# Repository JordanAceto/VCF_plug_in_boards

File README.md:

# Various Voltage Controlled Filter pcbs

- #### These small VCF "plug-in" boards each contain a filter "core". These are intended to be plugged into a motherboard which provides a +/- 12 volt power supply, input/output circuitry, and control voltage sources.
- #### They all share an identical mechanical and electrical format.
- #### The intended use is to make a bunch of different filters and then be able to easily try them out by swapping the filter plug-in boards into the motherboard.

## The mechanical format and pinout shared by all plug-in boards:

## Signal levels:
- #### The plug-in boards are expecting modular synthesizer level signals of around +/- 5 volts.
- #### Many filters have interesting resonance and distortion characteristics that depend on signal level. Experiment with increasing and decreasing the signal levels to find the sweet spots.
- #### The output signal may or may not be in phase with the input signal.

## CV signals:
- #### The motherboard is expected to provide a 0 to +2.048 volt cutoff frequency CV signal. The plug-in boards are designed to sweep through their entire range with this range, with 0 volts mapping to the lowest cutoff frequency (usually around 20Hz) and +2.048 volts mapping to the highest cutoff frequency (usually around 20kHz).
- #### The feedback CV from the motherboard uses the same range: 0 volts of feedback CV maps to "no feedback" and +2.048 volts of feedback CV maps to maximum feedback.
- #### The CV range of 0 to +2.048 volts was chosen becuase it allows the cutoff and feedback CV signals to be conveniently driven directly from a cheap MCP4822 DAC. Don't worry about an exact 2.048 volt range, the filters have trimmers to account for variations.
- #### If different scalings are desired it is usually fairly trivial to change some resistor values in the CV scaling circuits on the plug-in boards.

## Feedback considerations:
- #### The plug-in boards all have voltage controlled feedback. This makes it easier to swap them in and out of a motherboard without worrying about the type and value of feedback potentiometer.
- #### This also makes it easier to apply "Q-compensation" to 4-pole low pass filters that suffer from passband attenuation when feedback is increased.
- #### All 4-pole filters have some form of Q-compensation built in. The builder can usually adjust the amount of compensation, or choose no compensation at all by changing a single resistor.

## Calibration:
- #### Each plug-in board has calibration trimpots for modulation depth, center frequency, and feedback sensitivity.
- #### For filters that can track at 1 volt per octave, they can probably be trimmed to play in tune over a limited range, but the trimming may be fiddly. Emphasis has been placed on getting a nice sweep through the filters useful range, and not accurate tuning or temperature compensation.
- #### Calibration is a matter of taste, and any setup that sounds good to you is correct.
- #### Here is how I calibrate Low Pass Filters:
    1. Inject a 30Hz square wave onto the signal input while monitoring the signal output.
    2. Turn the cutoff CV and feedback CV signals all the way down (set them to zero volts).
    3. Adjust the **center** trim so that the signal just dissapears.
    4. Remove the signal input.
    5. Turn the cutoff CV to around 1/2 way up and turn the feedback CV all the way up.
    6. Adjust the **feedback** trim until self oscillation occurs.
    7. Turn the cutoff CV signal all the way up.
    8. Adjust the **depth** trim until the frequency of the self oscillation is around 20kHz.
    9. Sweep the cutoff frequency up and down and readjust the **feedback** trim as needed to get reliable self oscillation over the desired range. Note that some filters will not self oscillate over their whole frequency range.
    10. Now reinject the signal and listen to the filter while changing the cutoff and feedack CV signals. Readjust the trimmers to taste if desired.

- #### I use a similar strategy for other filter topologies like Phase Shifters. Without a self oscillation signal or a strong sense of "cutoff frequency", just adjust the trimmers so that the filter has a nice sweep and the feedback control feels good.
- #### The above calibration strategy is very quick and easy once you've done it a few times.

## Power supply considerations:
- #### The motherboard is expected to provide a +/-12 volt DC power supply.
- #### Current draw varies across the filter boards from a handfull of milliamps to a few 10's of milliamps.
- #### Ensure that the motherboard can supply at least 100mA or so on each rail.

## Starting new plug-in board pcbs:
- #### A template is provided to make it easy to start new plug-in board filters.
- #### This template contains a standard directory structure, and the start of a kicad project.
- #### The template kicad docs have the skeleton of the schematic and pcb.

## Project structure:
- #### Each filter plug-in board subdirectory follows a consistent structure:
    - #### `kicad_docs/` contains the files needed to open and edit the filter schematic and pcb layout using kicad.
    - #### `construction_docs/` contains a pdf copy of the schematic, an interactive BOM which can be opened in a web browser, and gerbers.
    - #### `pics/` contains a few rendered pics of the pcb.
- #### Basically, if you want to edit the filter go into `kicad_docs/`, if you want to build the filter go into `construction_docs/`.
- #### Note that the filters may be a work in progress and may not contain complete documentation until they are done.
- #### See the board status checklist below, any board that is not checked all the way across is likely to contain errors. Boards that are all checked all the way across are safe to build.

## Status of the boards:

Board | breadboarded | schematic | pcb layout | built and tested | documentation
------|--------------|-----------|------------|------------------|---------------
[2164 phasor](https://github.com/JordanAceto/VCF_plug_in_boards/tree/master/2164_phasor_plug_in_board)       | &#9745; | &#9745; | &#9745; | &#9745; | &#9745;
[2164 LPF](https://github.com/JordanAceto/VCF_plug_in_boards/tree/master/2164_4_pole_LPF_plug_in_board)       | &#9745; | &#9745; | &#9745; | &#9745; | &#9745;
[2164 SVF](https://github.com/JordanAceto/VCF_plug_in_boards/tree/master/2164_SVF_plug_in_board)       | &#9745; | &#9745; | &#9745; | &#9745; | &#9745;
[arp 4072 LPF](https://github.com/JordanAceto/VCF_plug_in_boards/tree/master/arp_4072_LPF_plug_in_board)      | &#9745; | &#9745; | &#9745; | &#9745; | &#9745;
[CEM3320 LPF](https://github.com/JordanAceto/VCF_plug_in_boards/tree/master/CEM3320_LPF_plug_in_board)       | &#9745; | &#9745; | &#9745; | &#9745; | &#9745;
[haible 2040 LPF](https://github.com/JordanAceto/VCF_plug_in_boards/tree/master/haible_2040_LPF_plug_in_board)   | &#9745; | &#9744; | &#9744; | &#9744; | &#9744;
[haible tau phasor](https://github.com/JordanAceto/VCF_plug_in_boards/tree/master/haible_tau_phaser_plug_in_board/kicad_docs) | &#9744; | &#9744; | &#9744; | &#9744; | &#9744;
[Late MS20 VCF](https://github.com/JordanAceto/VCF_plug_in_boards/tree/master/late_MS20_VCF_plug_in_board)       | &#9745; | &#9745; | &#9745; | &#9745; | &#9745;
[minimoog LPF](https://github.com/JordanAceto/VCF_plug_in_boards/tree/master/minimoog_LPF_plug_in_board)      | &#9745; | &#9745; | &#9745; | &#9745; | &#9745;
[mutron 3 SVF](https://github.com/JordanAceto/VCF_plug_in_boards/tree/master/mutron_III_plug_in_board)      | &#9745; | &#9745; | &#9745; | &#9745; | &#9745;
[optical phasor](https://github.com/JordanAceto/VCF_plug_in_boards/tree/master/optical_phasor_plug_in_board)    | &#9745; | &#9745; | &#9745; | &#9745; | &#9745;
[SSI2140 LPF](https://github.com/JordanAceto/VCF_plug_in_boards/tree/master/SSI2140_LPF_plug_in_board) | &#9745; | &#9745; | &#9745; | &#9745; | &#9745;

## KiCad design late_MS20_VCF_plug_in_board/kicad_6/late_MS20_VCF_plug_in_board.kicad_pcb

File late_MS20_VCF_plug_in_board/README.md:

# Late MS20 style VCF Plug-In Board

Small MS20 based low pass/high pass filter PCB, designed to plug into a larger motherboard.

## Details

MS20 based LPF/HPF with voltage controlled feedback. This PCB includes the audio path and CV inputs for frequency and feedback, but does not include any modulation sources.

The intended use for this board is to plug in to a larger motherboard which contains slots for one or more of these plug-in boards, as well as modulation sources, panel controls, and input/output routing.

High pass or Low pass mode is selected by placing two jumpers as indicated on the silkscreen.

## Inputs

-Audio in: dry audio input to be filtered.

-Frequency CV in: 0 volts to +2.048 volts, higher voltage = higher sweep.

-Feedback CV in: 0 volts to +2.048 volts, higher voltage = more feedback.

## Outputs

-Audio out: filtered audio output.

## Filter mode selection

- This filter has two filter modes available: Low Pass and High Pass.

- One mode at a time can be selected by placing two jumpers according to the silkscreen.

## Power Supply Requirements

A bipolar 12 volt power supply is required. This will typically come from the motherboard.

## Calibration

- See the top level README for calibration instructions.

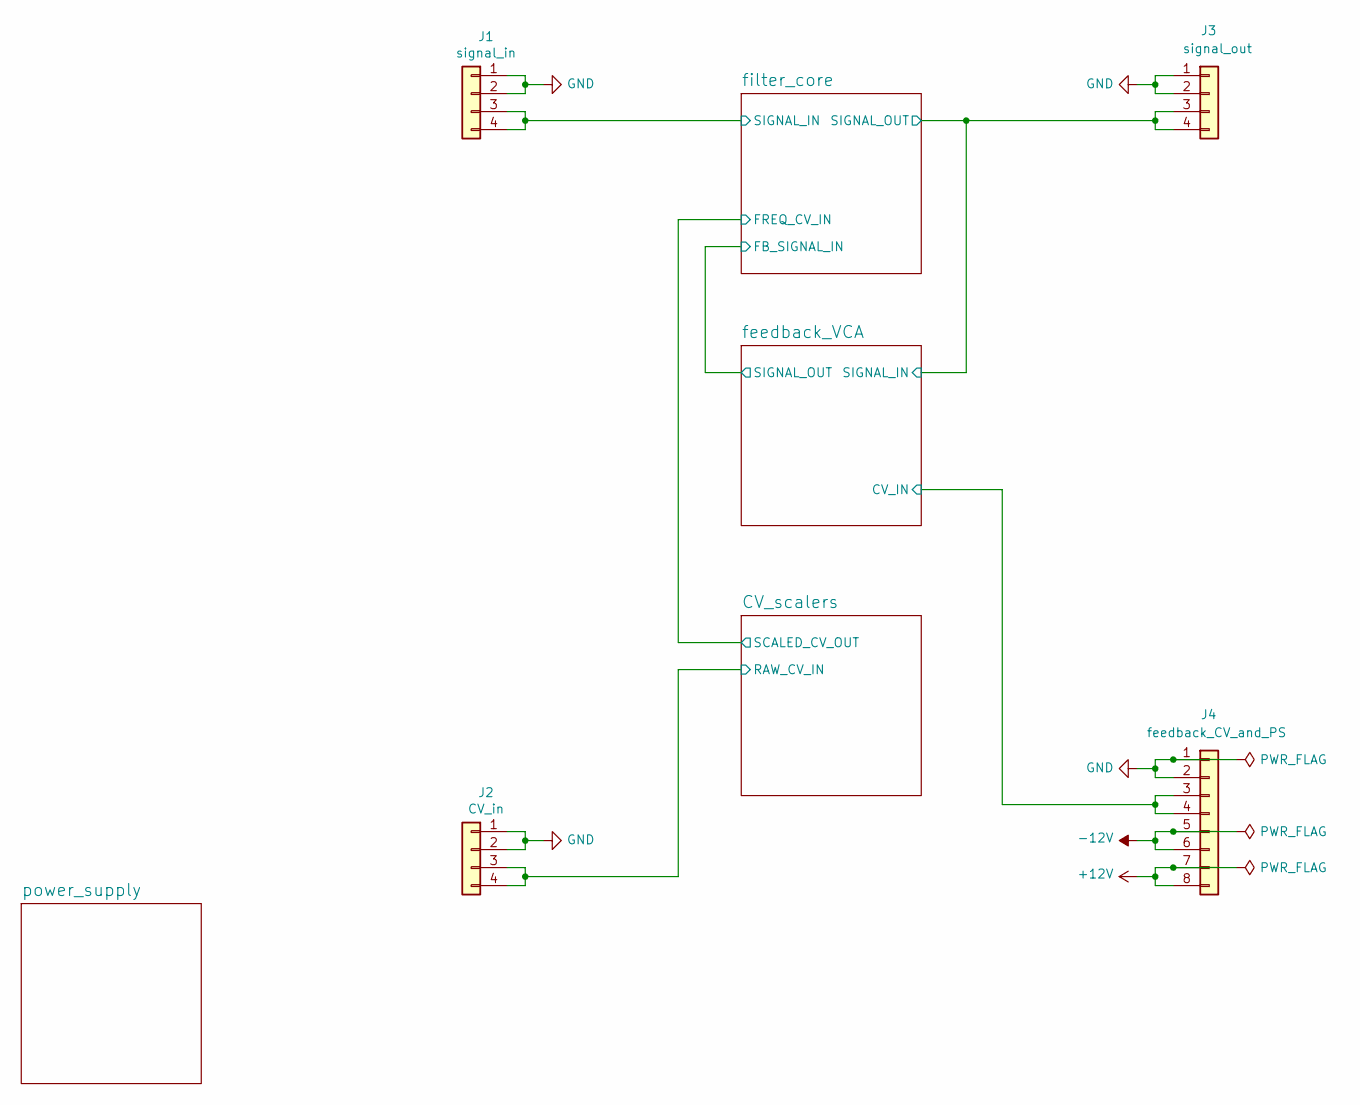
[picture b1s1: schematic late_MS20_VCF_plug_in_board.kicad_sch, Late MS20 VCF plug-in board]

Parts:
J1: signal_in; PinHeader_1x04_P2.54mm_Vertical
J2: CV_in; PinHeader_1x04_P2.54mm_Vertical
J3: signal_out; PinHeader_1x04_P2.54mm_Vertical
J4: feedback_CV_and_PS; PinHeader_1x08_P2.54mm_Vertical

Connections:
+12V: J4.7, J4.8; also elsewhere on the board
-12V: J4.5, J4.6; also elsewhere on the board
/CV_scalers/RAW_CV_IN: J2.3, J2.4; also elsewhere on the board
/feedback_VCA/CV_IN: J4.3, J4.4; also elsewhere on the board
/feedback_VCA/SIGNAL_IN: J3.3, J3.4; also elsewhere on the board
/filter_core/SIGNAL_IN: J1.3, J1.4; also elsewhere on the board
GND: J1.1, J1.2, J2.1, J2.2, J3.1, J3.2, J4.1, J4.2; also elsewhere on the board

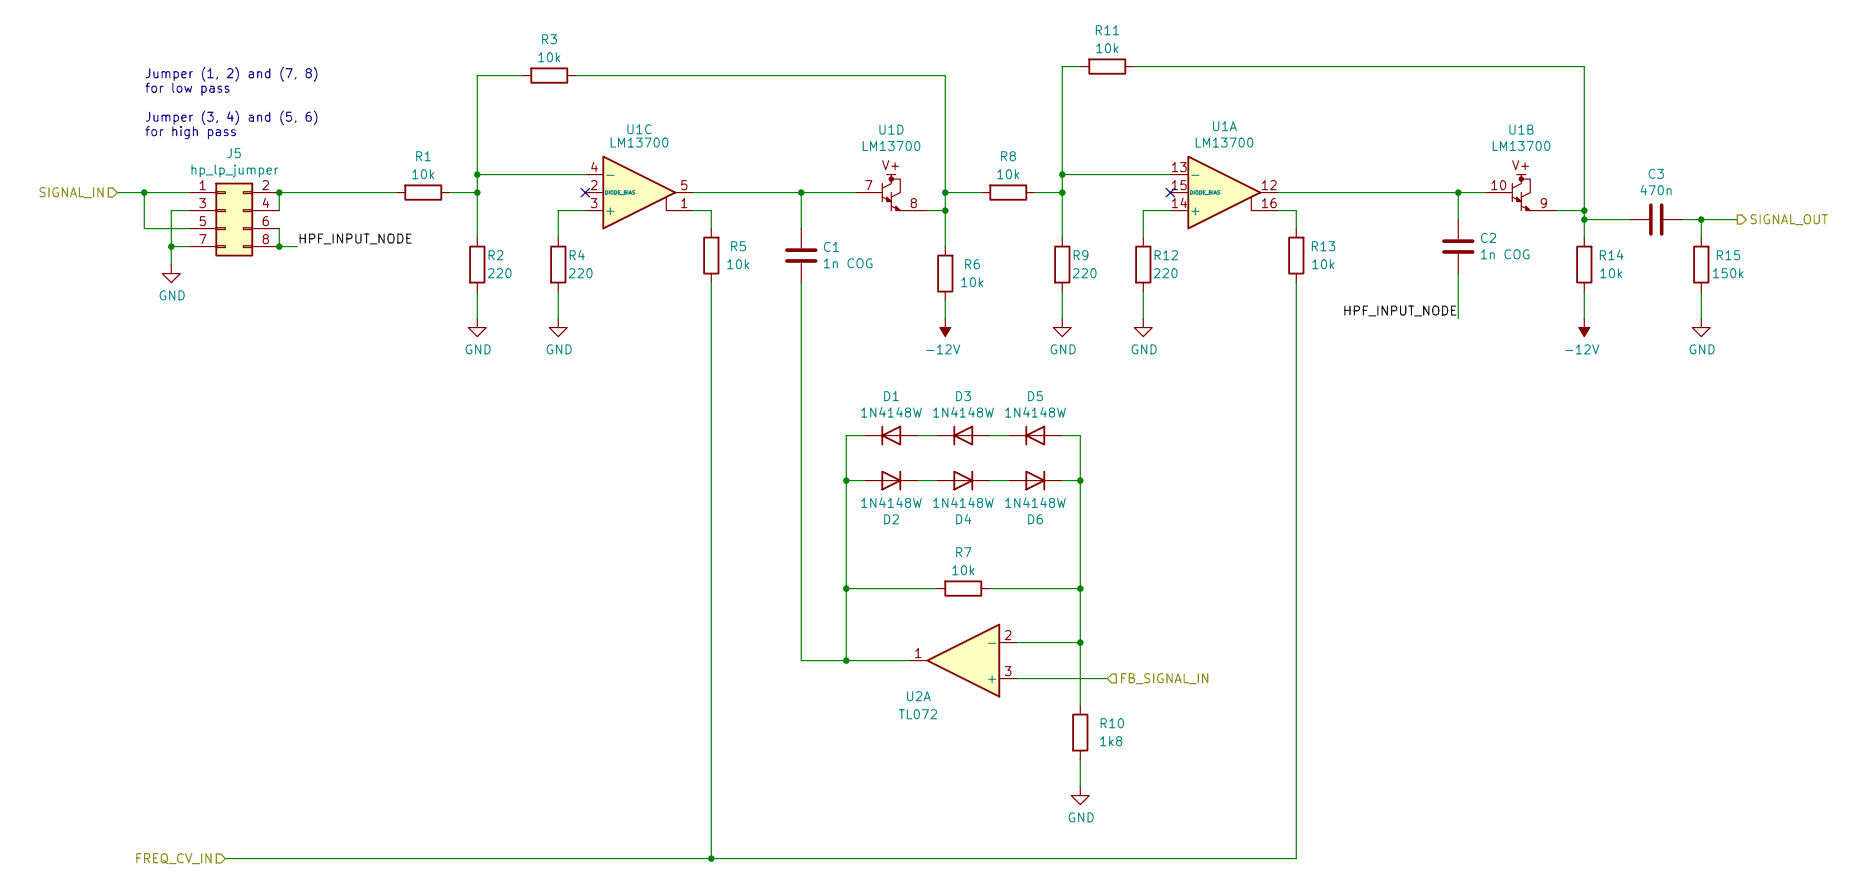
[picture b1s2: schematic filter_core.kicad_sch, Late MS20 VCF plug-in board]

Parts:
C1, C2: 1n COG; C_0805_2012Metric
C3: 470n; C_Rect_L7.0mm_W3.5mm_P5.00mm
D1, D2, D3, D4, D5, D6: 1N4148W; D_SOD-123
J5: hp_lp_jumper; PinHeader_2x04_P2.54mm_Vertical
R1, R3, R5, R6, R7, R8, R11, R13, R14: 10k; R_0603_1608Metric
R2, R4, R9, R12: 220; R_0603_1608Metric
R10: 1k8; R_0603_1608Metric
R15: 150k; R_0603_1608Metric
U1: LM13700; SOIC-16_3.9x9.9mm_P1.27mm
U2: TL072; SOIC-8_3.9x4.9mm_P1.27mm

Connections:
-12V: R6.1, R14.1; also elsewhere on the board
/CV_scalers/SCALED_CV_OUT: R5.1, R13.1; also elsewhere on the board
/feedback_VCA/SIGNAL_IN: C3.1, R15.2; also elsewhere on the board
/feedback_VCA/SIGNAL_OUT: U2.3 (+); also elsewhere on the board
/filter_core/HPF_INPUT_NODE: C2.2, J5.6, J5.8
/filter_core/SIGNAL_IN: J5.1, J5.5; also elsewhere on the board
GND: J5.3, J5.7, R2.2, R4.2, R9.2, R10.2, R12.2, R15.1; also elsewhere on the board
unnamed: C1.1, U1.5, U1.7
unnamed: C1.2, D1.1 (K), D2.2 (A), R7.2, U2.1
unnamed: C2.1, U1.10, U1.12
unnamed: C3.2, R11.1, R14.2, U1.9
unnamed: D1.2 (A), D3.1 (K)
unnamed: D2.1 (K), D4.2 (A)
unnamed: D3.2 (A), D5.1 (K)
unnamed: D4.1 (K), D6.2 (A)
unnamed: D5.2 (A), D6.1 (K), R7.1, R10.1, U2.2 (-)
unnamed: J5.2, J5.4, R1.2
unnamed: R1.1, R2.1, R3.2, U1.4 (-)
unnamed: R3.1, R6.2, R8.2, U1.8
unnamed: R4.1, U1.3 (+)
unnamed: R5.2, U1.1
unnamed: R8.1, R9.1, R11.2, U1.13 (-)
unnamed: R12.1, U1.14 (+)
unnamed: R13.2, U1.16

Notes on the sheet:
Jumper (1, 2) and (7, 8) for low pass Jumper (3, 4) and (5, 6) for high pass

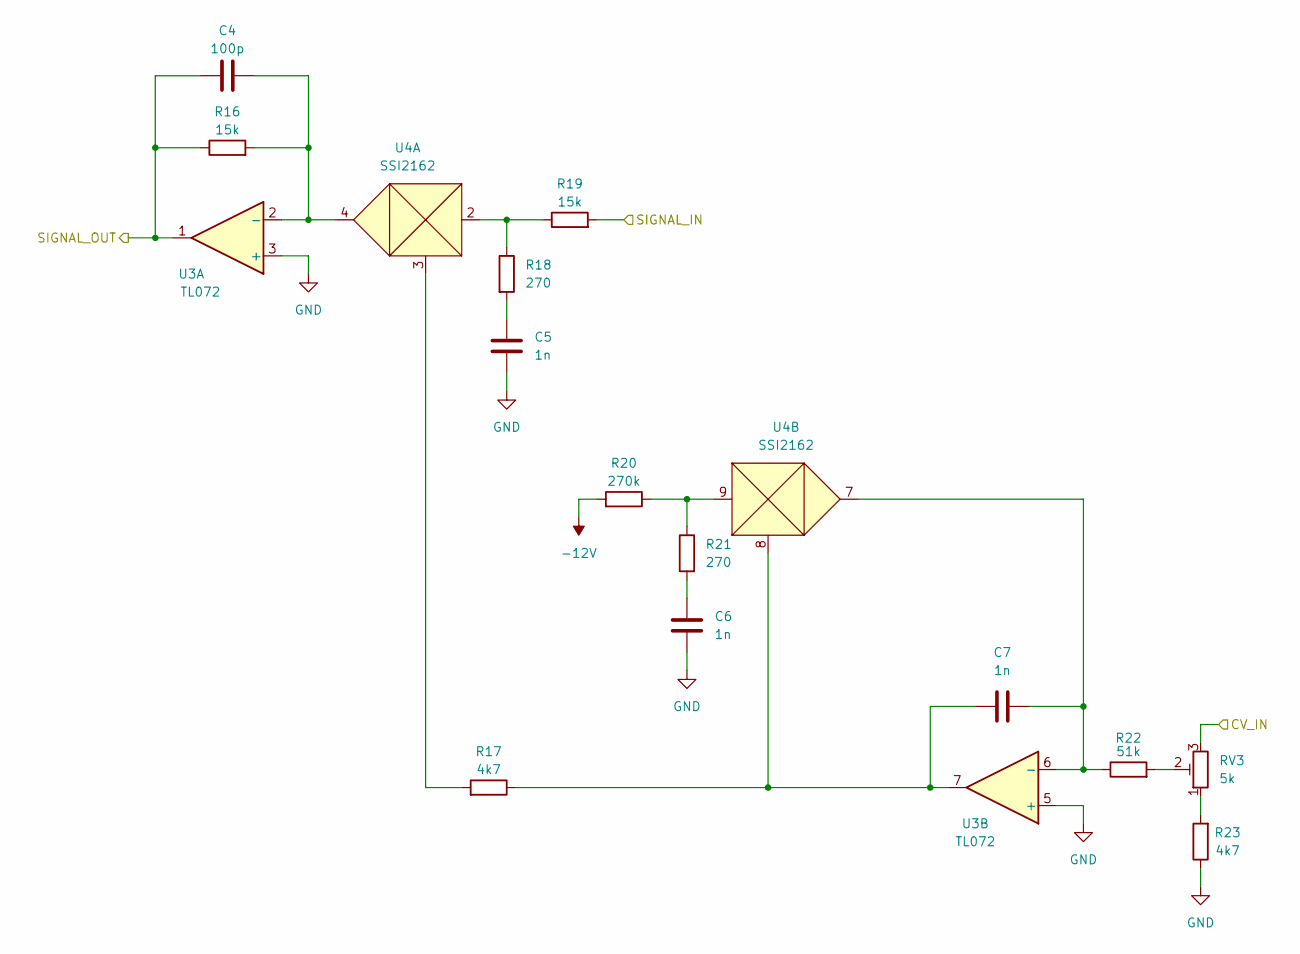
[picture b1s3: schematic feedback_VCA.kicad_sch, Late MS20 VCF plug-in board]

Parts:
C4: 100p; C_0603_1608Metric
C5, C6, C7: 1n; C_0603_1608Metric
R16, R19: 15k; R_0603_1608Metric
R17, R23: 4k7; R_0603_1608Metric
R18, R21: 270; R_0603_1608Metric
R20: 270k; R_0603_1608Metric
R22: 51k; R_0603_1608Metric
RV3: 5k; Potentiometer_Bourns_3296W_Vertical
U3: TL072; SOIC-8_3.9x4.9mm_P1.27mm
U4: SSI2162; SSOP-10_3.9x4.9mm_P1.00mm

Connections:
-12V: R20.2; also elsewhere on the board
/feedback_VCA/CV_IN: RV3.3; also elsewhere on the board
/feedback_VCA/SIGNAL_IN: R19.2; also elsewhere on the board
/feedback_VCA/SIGNAL_OUT: C4.1, R16.1, U3.1; also elsewhere on the board
GND: C5.2, C6.2, R23.1, U3.3 (+), U3.5 (+); also elsewhere on the board
unnamed: C4.2, R16.2, U3.2 (-), U4.4
unnamed: C5.1, R18.2
unnamed: C6.1, R21.2
unnamed: C7.1, R17.1, U3.7, U4.8
unnamed: C7.2, R22.1, U3.6 (-), U4.7
unnamed: R17.2, U4.3
unnamed: R18.1, R19.1, U4.2
unnamed: R20.1, R21.1, U4.9
unnamed: R22.2, RV3.2
unnamed: R23.2, RV3.1

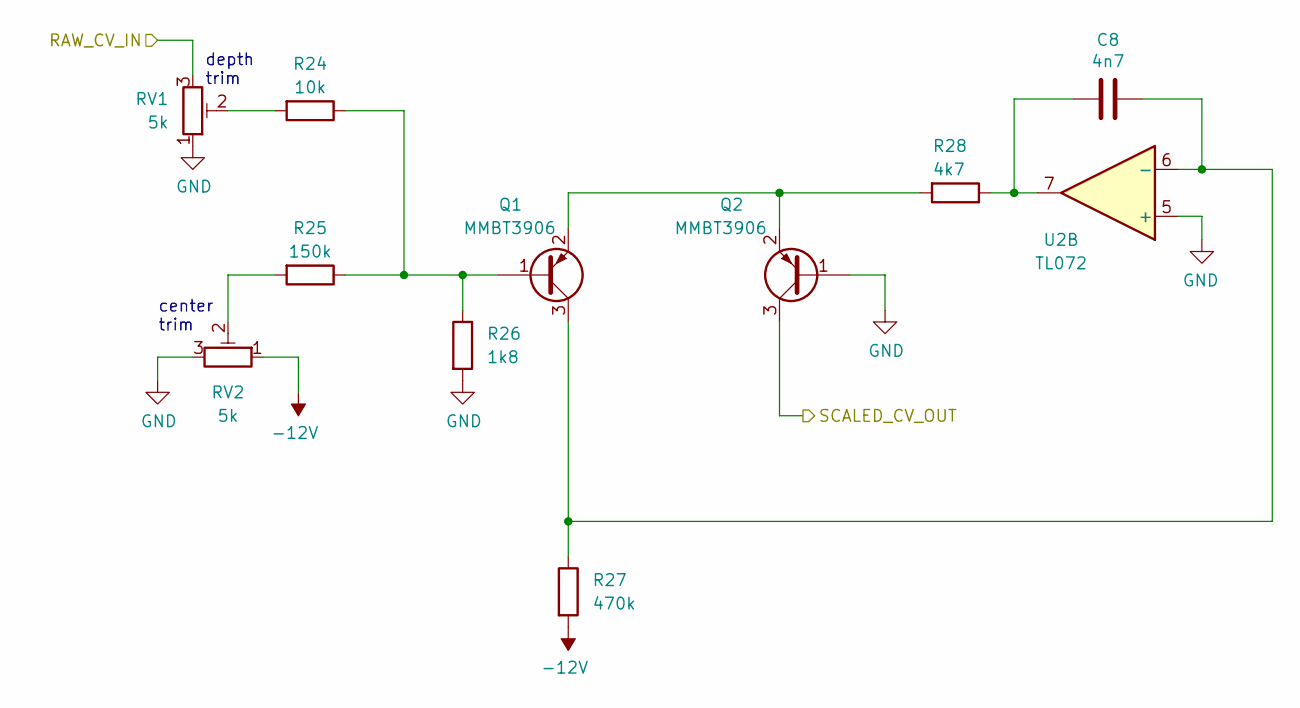
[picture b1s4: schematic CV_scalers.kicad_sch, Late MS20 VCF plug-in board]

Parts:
C8: 4n7; C_0603_1608Metric
Q1, Q2: MMBT3906; SOT-23
R24: 10k; R_0603_1608Metric
R25: 150k; R_0603_1608Metric
R26: 1k8; R_0603_1608Metric
R27: 470k; R_0603_1608Metric
R28: 4k7; R_0603_1608Metric
RV1, RV2: 5k; Potentiometer_Bourns_3296W_Vertical
U2: TL072; SOIC-8_3.9x4.9mm_P1.27mm

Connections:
-12V: R27.2, RV2.1; also elsewhere on the board
/CV_scalers/RAW_CV_IN: RV1.3; also elsewhere on the board
/CV_scalers/SCALED_CV_OUT: Q2.3 (C); also elsewhere on the board
GND: Q2.1 (B), R26.2, RV1.1, RV2.3, U2.5 (+); also elsewhere on the board
unnamed: C8.1, R28.1, U2.7
unnamed: C8.2, Q1.3 (C), R27.1, U2.6 (-)
unnamed: Q1.1 (B), R24.1, R25.1, R26.1
unnamed: Q1.2 (E), Q2.2 (E), R28.2
unnamed: R24.2, RV1.2
unnamed: R25.2, RV2.2

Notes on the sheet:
center trim
depth trim

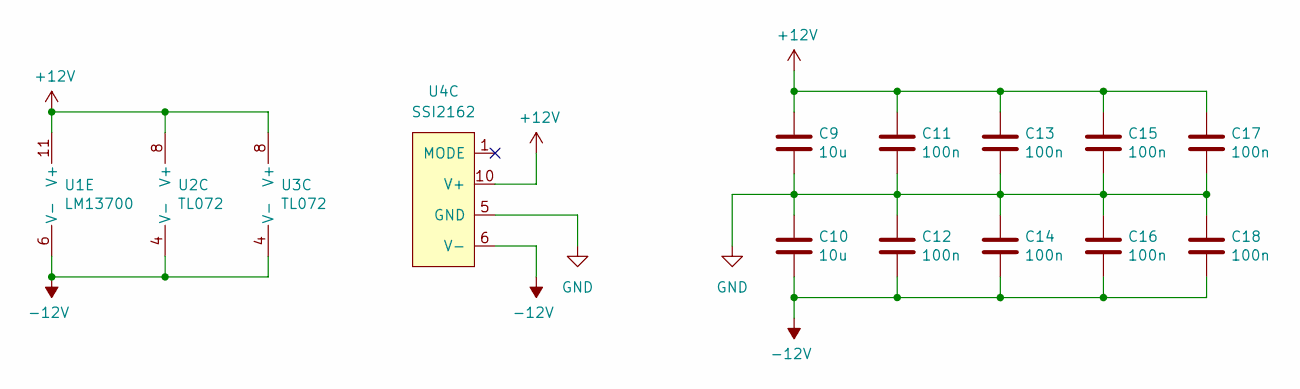
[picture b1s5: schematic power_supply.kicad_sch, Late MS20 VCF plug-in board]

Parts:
C9, C10: 10u; C_0805_2012Metric
C11, C12, C13, C14, C15, C16, C17, C18: 100n; C_0603_1608Metric
U1: LM13700; SOIC-16_3.9x9.9mm_P1.27mm
U2, U3: TL072; SOIC-8_3.9x4.9mm_P1.27mm
U4: SSI2162; SSOP-10_3.9x4.9mm_P1.00mm

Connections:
+12V: C9.1, C11.1, C13.1, C15.1, C17.1, U1.11 (V+), U2.8 (V+), U3.8 (V+), U4.10 (V+); also elsewhere on the board
-12V: C10.2, C12.2, C14.2, C16.2, C18.2, U1.6 (V-), U2.4 (V-), U3.4 (V-), U4.6 (V-); also elsewhere on the board
GND: C9.2, C10.1, C11.2, C12.1, C13.2, C14.1, C15.2, C16.1, C17.2, C18.1, U4.5 (GND); also elsewhere on the board

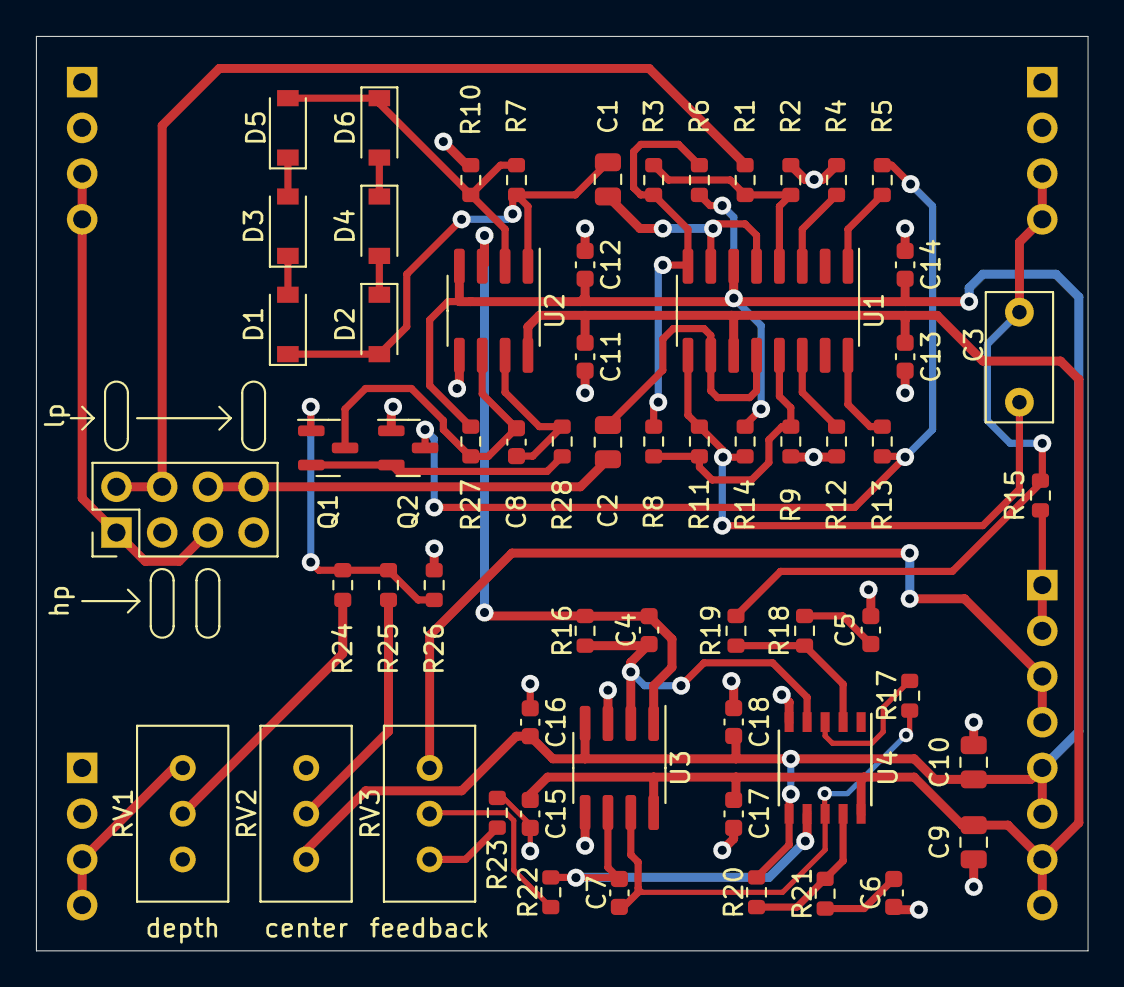
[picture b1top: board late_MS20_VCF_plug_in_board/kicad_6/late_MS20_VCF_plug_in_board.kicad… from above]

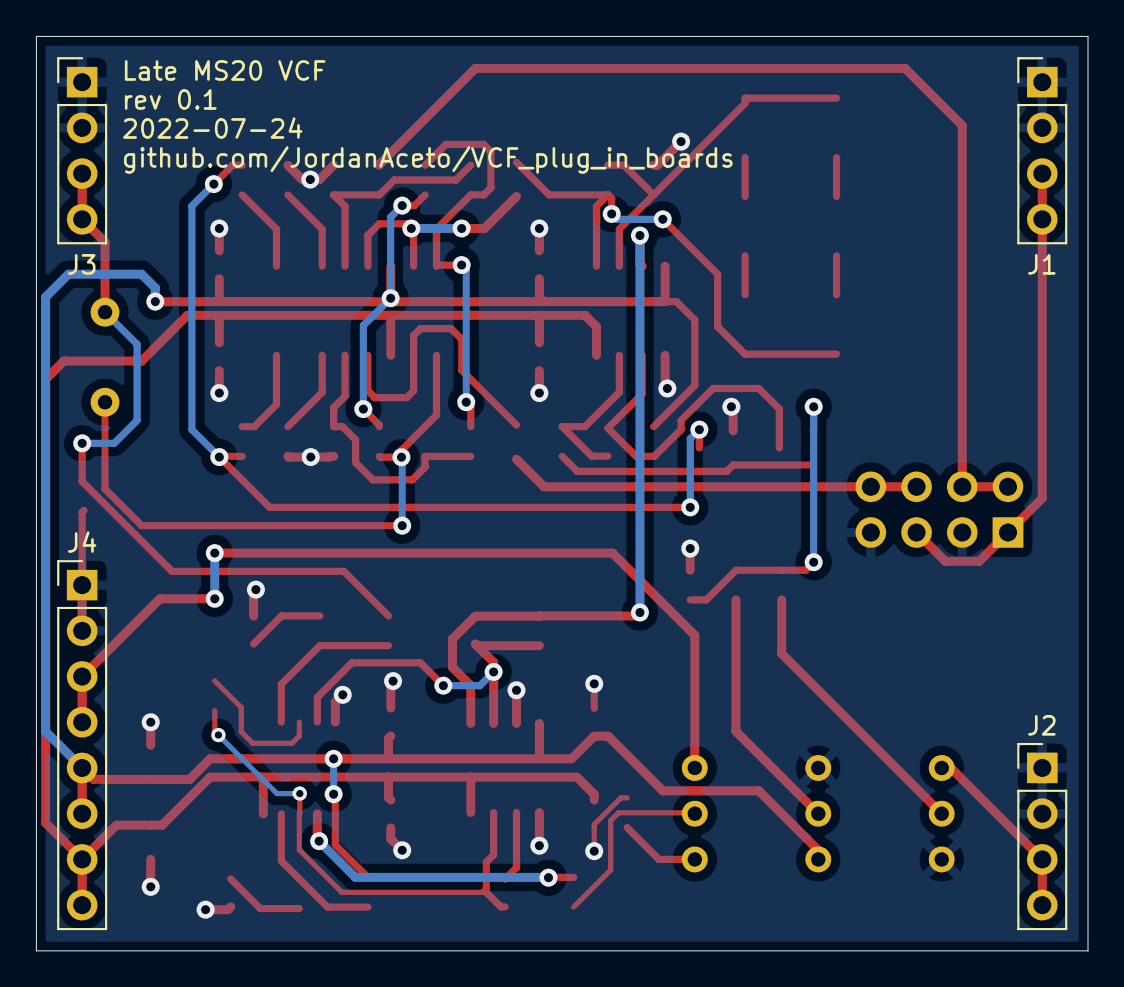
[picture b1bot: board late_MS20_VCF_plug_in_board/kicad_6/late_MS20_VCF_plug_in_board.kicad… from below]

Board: 2 copper layers, 58.4 x 50.8 mm, 66 parts (4 on the bottom side), 43 nets.

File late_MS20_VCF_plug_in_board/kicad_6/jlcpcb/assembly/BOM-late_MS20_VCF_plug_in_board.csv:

Comment,Designator,Footprint,LCSC
100n,"C11,C12,C13,C14,C15,C16,C17,C18",C_0603_1608Metric,C14663
100p,C4,C_0603_1608Metric,C14858
1n,"C5,C6,C7",C_0603_1608Metric,C1588
150k,"R15,R25",R_0603_1608Metric,C22807
15k,"R16,R19",R_0603_1608Metric,C22809
220,"R12,R2,R4,R9",R_0603_1608Metric,C22962
270k,R20,R_0603_1608Metric,C22965
270,"R18,R21",R_0603_1608Metric,C22966
4k7,"R17,R23,R28",R_0603_1608Metric,C23162
470k,R27,R_0603_1608Metric,C23178
51k,R22,R_0603_1608Metric,C23196
10k,"R1,R11,R13,R14,R24,R3,R5,R6,R7,R8",R_0603_1608Metric,C25804
1k8,"R10,R26",R_0603_1608Metric,C4177
10u,"C10,C9",C_0805_2012Metric,C440198
4n7,C8,C_0603_1608Metric,C53987
TL072,"U2,U3",SOIC-8_3.9x4.9mm_P1.27mm,C6961
1N4148W,"D1,D2,D3,D4,D5,D6",D_SOD-123,C81598

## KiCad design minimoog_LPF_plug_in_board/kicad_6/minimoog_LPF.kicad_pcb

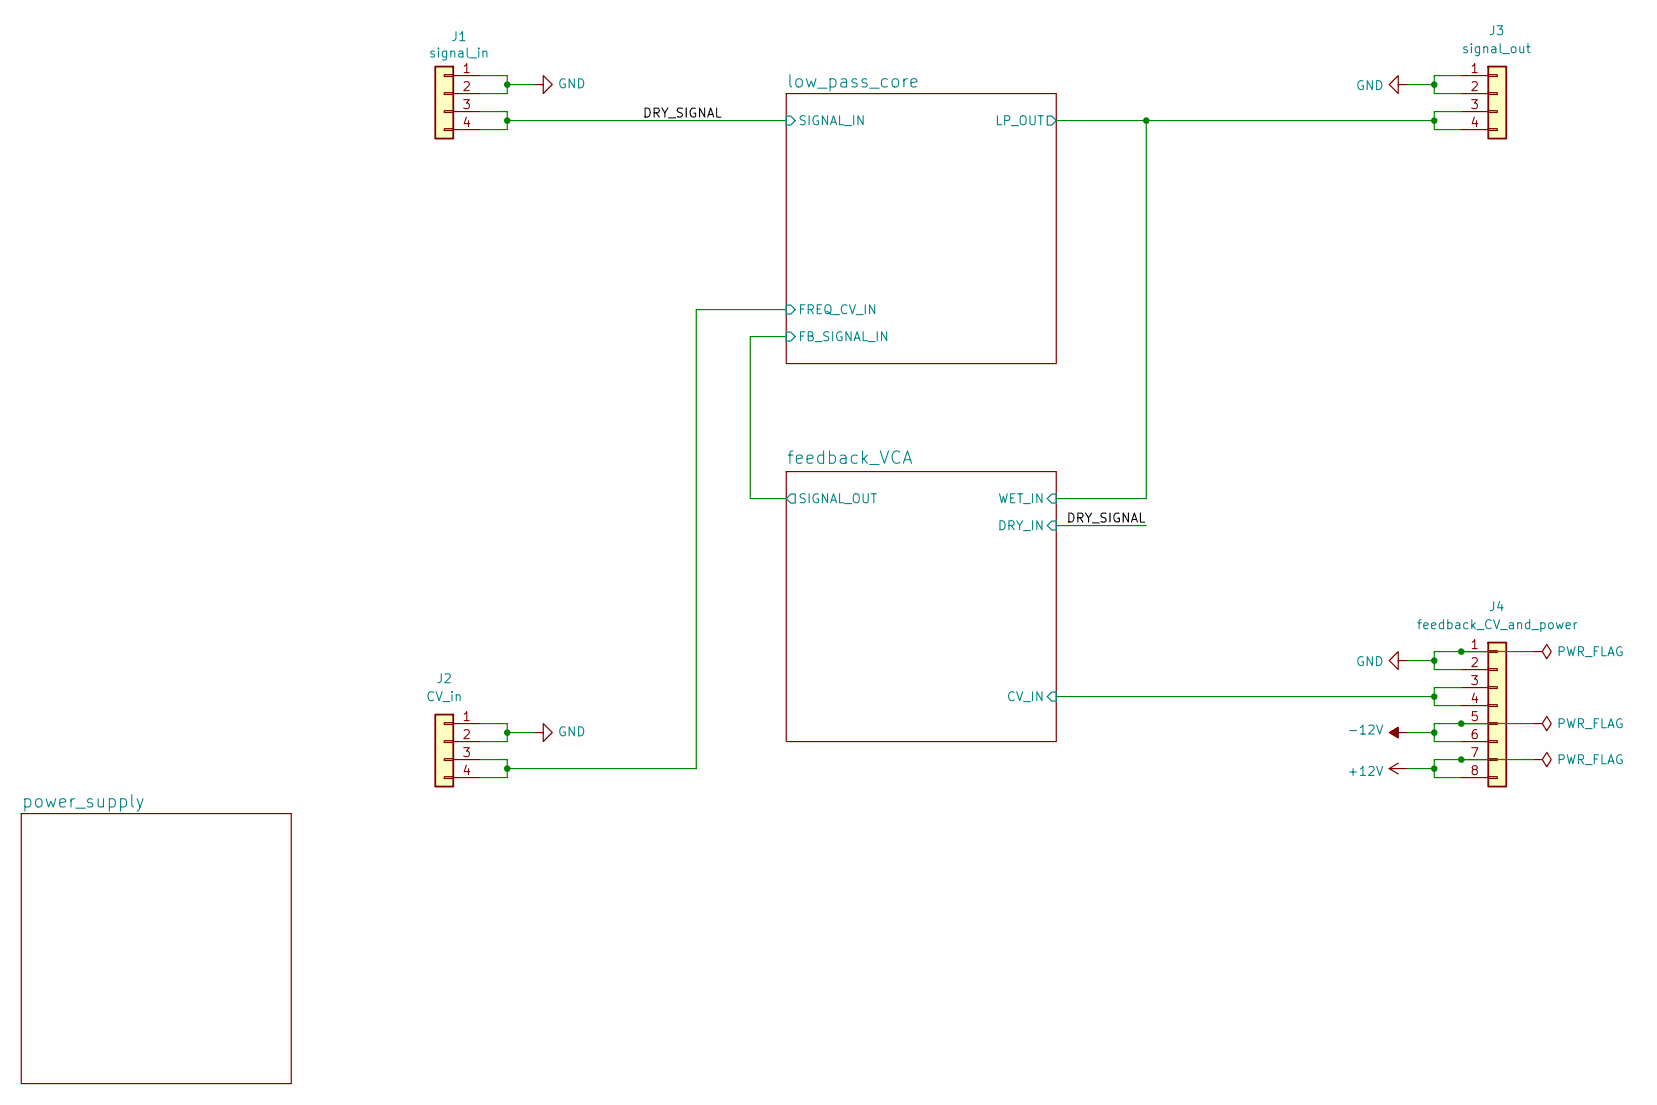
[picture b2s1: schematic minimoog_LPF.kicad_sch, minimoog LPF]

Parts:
J1: signal_in; PinHeader_1x04_P2.54mm_Vertical
J2: CV_in; PinHeader_1x04_P2.54mm_Vertical
J3: signal_out; PinHeader_1x04_P2.54mm_Vertical
J4: feedback_CV_and_power; PinHeader_1x08_P2.54mm_Vertical

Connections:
+12V: J4.7, J4.8; also elsewhere on the board
-12V: J4.5, J4.6; also elsewhere on the board
/DRY_SIGNAL: J1.3, J1.4; also elsewhere on the board
/feedback_VCA/CV_IN: J4.3, J4.4; also elsewhere on the board
/feedback_VCA/WET_IN: J3.3, J3.4; also elsewhere on the board
/low_pass_core/FREQ_CV_IN: J2.3, J2.4; also elsewhere on the board
GND: J1.1, J1.2, J2.1, J2.2, J3.1, J3.2, J4.1, J4.2; also elsewhere on the board

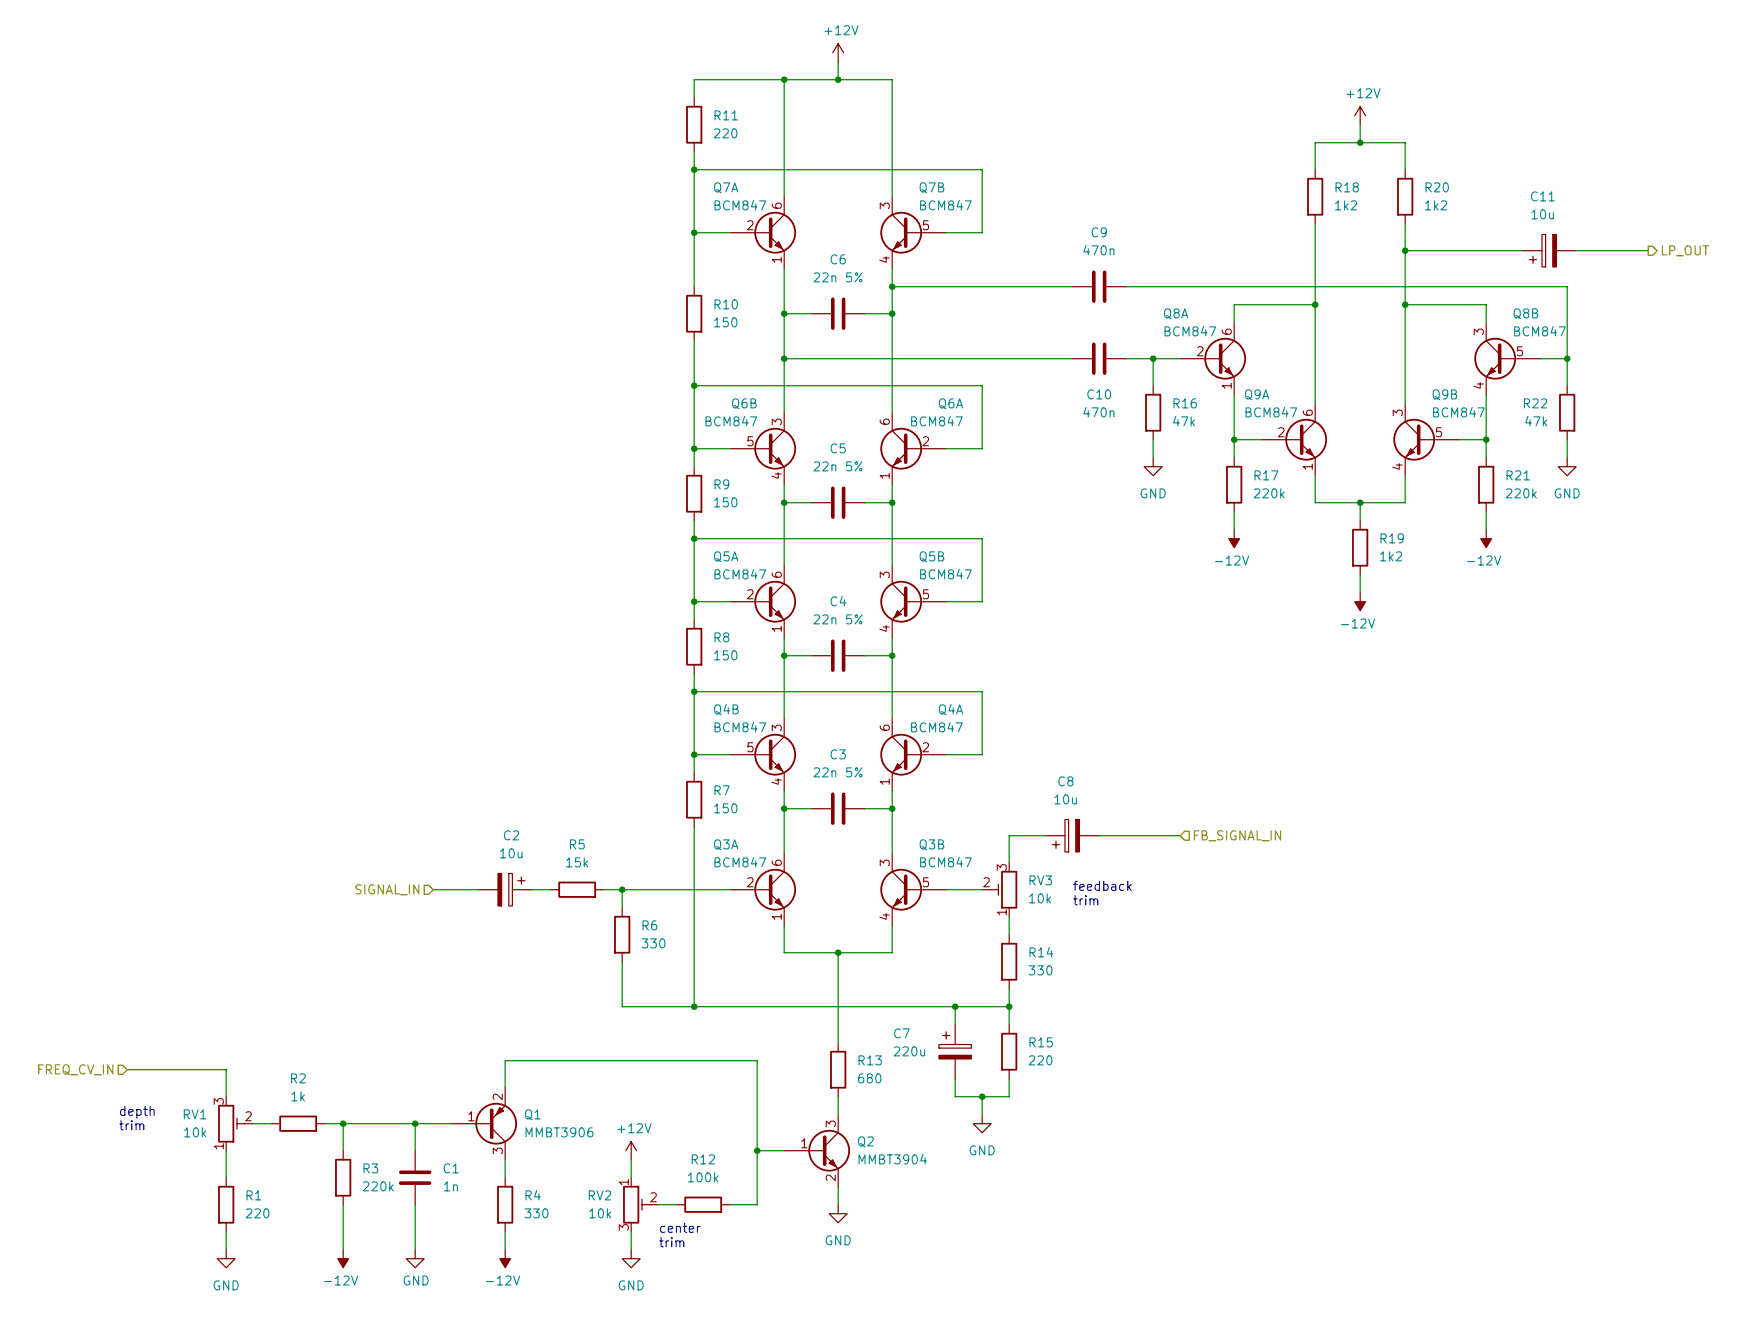
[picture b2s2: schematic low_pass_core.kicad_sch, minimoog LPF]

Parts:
C1: 1n; C_0603_1608Metric
C2, C8, C11: 10u; CP_Radial_D6.3mm_P2.50mm
C3, C4, C5, C6: 22n 5%; C_0805_2012Metric
C7: 220u; CP_Radial_D6.3mm_P2.50mm
C9, C10: 470n; C_Rect_L7.0mm_W3.5mm_P5.00mm
Q1: MMBT3906; SOT-23
Q2: MMBT3904; SOT-23
Q3, Q4, Q5, Q6, Q7, Q8, Q9: BCM847; SOT-363_SC-70-6
R1, R11, R15: 220; R_0603_1608Metric
R2: 1k; R_0603_1608Metric
R3, R17, R21: 220k; R_0603_1608Metric
R4, R6, R14: 330; R_0603_1608Metric
R5: 15k; R_0603_1608Metric
R7, R8, R9, R10: 150; R_0603_1608Metric
R12: 100k; R_0603_1608Metric
R13: 680; R_0603_1608Metric
R16, R22: 47k; R_0603_1608Metric
R18, R19, R20: 1k2; R_0603_1608Metric
RV1, RV2, RV3: 10k; Potentiometer_Bourns_3296W_Vertical

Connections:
+12V: Q7.3 (C), Q7.6 (C), R11.1, R18.1, R20.1, RV2.1; also elsewhere on the board
-12V: R3.2, R4.2, R17.2, R19.2, R21.2; also elsewhere on the board
/DRY_SIGNAL: C2.2; also elsewhere on the board
/feedback_VCA/SIGNAL_OUT: C8.2; also elsewhere on the board
/feedback_VCA/WET_IN: C11.2; also elsewhere on the board
/low_pass_core/FREQ_CV_IN: RV1.3; also elsewhere on the board
GND: C1.1, C7.2, Q2.2 (E), R1.2, R15.2, R16.2, R22.2, RV2.3; also elsewhere on the board
unnamed: C1.2, Q1.1 (B), R2.2, R3.1
unnamed: C2.1, R5.1
unnamed: C3.1, Q3.6 (C), Q4.4 (E)
unnamed: C3.2, Q3.3 (C), Q4.1 (E)
unnamed: C4.1, Q4.3 (C), Q5.1 (E)
unnamed: C4.2, Q4.6 (C), Q5.4 (E)
unnamed: C5.1, Q5.6 (C), Q6.4 (E)
unnamed: C5.2, Q5.3 (C), Q6.1 (E)
unnamed: C6.2, C9.1, Q6.6 (C), Q7.4 (E)
unnamed: C7.1, R6.2, R7.2, R14.2, R15.1
unnamed: C8.1, RV3.3
unnamed: C9.2, Q8.5 (B), R22.1
unnamed: C6.1, C10.1, Q6.3 (C), Q7.1 (E)
unnamed: C10.2, Q8.2 (B), R16.1
unnamed: C11.1, Q8.3 (C), Q9.3 (C), R20.2
unnamed: Q1.2 (E), Q2.1 (B), R12.2
unnamed: Q1.3 (C), R4.1
unnamed: Q2.3 (C), R13.2
unnamed: Q3.1 (E), Q3.4 (E), R13.1
unnamed: Q3.2 (B), R5.2, R6.1
unnamed: Q3.5 (B), RV3.2
unnamed: Q4.2 (B), Q4.5 (B), R7.1, R8.2
unnamed: Q5.2 (B), Q5.5 (B), R8.1, R9.2
unnamed: Q6.2 (B), Q6.5 (B), R9.1, R10.2
unnamed: Q7.2 (B), Q7.5 (B), R10.1, R11.2
unnamed: Q8.1 (E), Q9.2 (B), R17.1
unnamed: Q8.4 (E), Q9.5 (B), R21.1
unnamed: Q8.6 (C), Q9.6 (C), R18.2
unnamed: Q9.1 (E), Q9.4 (E), R19.1
unnamed: R1.1, RV1.1
unnamed: R2.1, RV1.2
unnamed: R12.1, RV2.2
unnamed: R14.1, RV3.1

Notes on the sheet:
depth trim
feedback trim
center trim

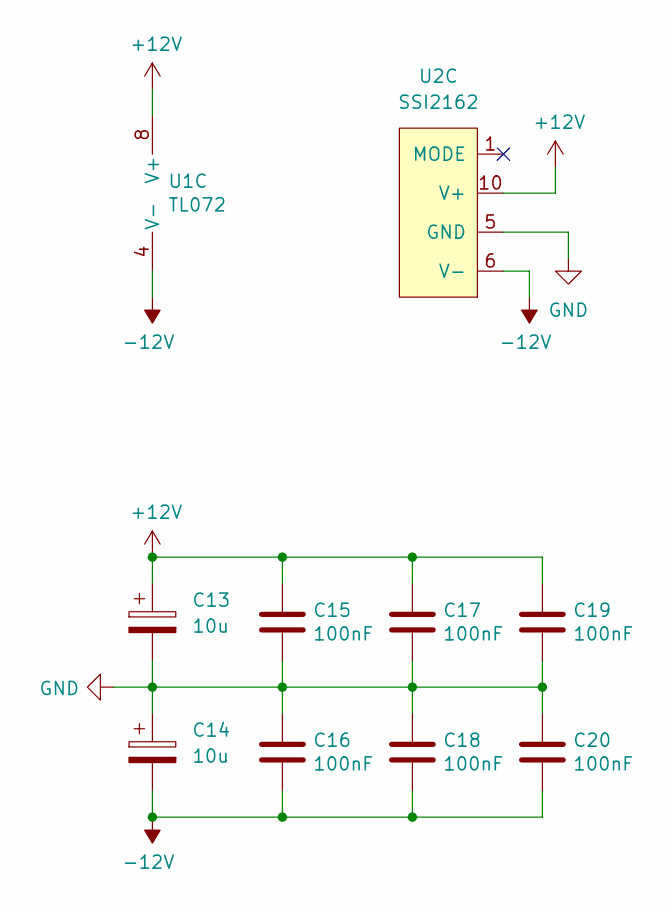
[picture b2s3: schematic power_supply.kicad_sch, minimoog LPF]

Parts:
C13, C14: 10u; CP_Radial_D6.3mm_P2.50mm
C15, C16, C17, C18, C19, C20: 100nF; C_0603_1608Metric
U1: TL072; SOIC-8_3.9x4.9mm_P1.27mm
U2: SSI2162; SSOP-10_3.9x4.9mm_P1.00mm

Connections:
+12V: C13.1, C15.1, C17.1, C19.1, U1.8 (V+), U2.10 (V+); also elsewhere on the board
-12V: C14.2, C16.2, C18.2, C20.2, U1.4 (V-), U2.6 (V-); also elsewhere on the board
GND: C13.2, C14.1, C15.2, C16.1, C17.2, C18.1, C19.2, C20.1, U2.5 (GND); also elsewhere on the board

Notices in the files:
2164_4_pole_LPF_plug_in_board/kicad_docs/CV_scaler.sch:
creativecommons.org/licenses/by/4.0
License: CC by 4.0
